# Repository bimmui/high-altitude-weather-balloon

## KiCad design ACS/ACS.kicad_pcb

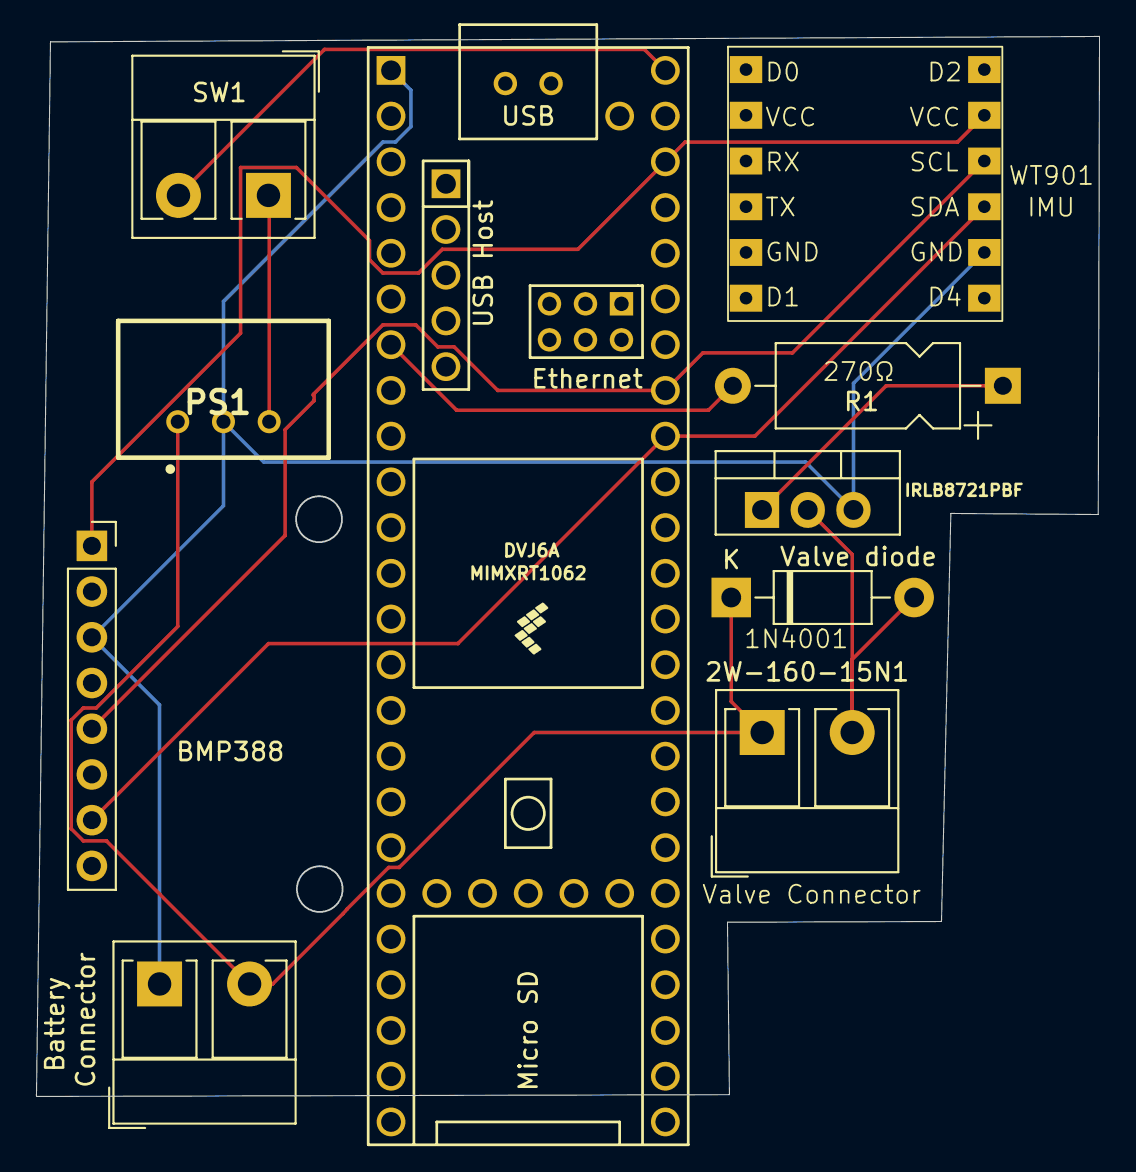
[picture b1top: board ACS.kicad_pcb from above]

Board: 2 copper layers, 59.0 x 58.8 mm, 10 parts (0 on the bottom side), 9 nets.

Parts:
2W-160-15N1: TerminalBlock_RND_205-00276_1x02_P5.00mm_Vertical
BMP388: PinSocket_1x08_P2.54mm_Vertical
Battery: Battery Screw_Terminal_01x02; TerminalBlock_RND_205-00276_1x02_P5.00mm_Vertical
IRLB8721PBF: IRLB8721PBF; TO-220-3_Vertical
PS1: TSR_1-2450; TSR-1-24120
R1: 270; CP_Axial_L10.0mm_D4.5mm_P15.00mm_Horizontal
SW1: SW_DPST_x2; TerminalBlock_RND_205-00276_1x02_P5.00mm_Vertical
U1: Teensy4.1; Teensy41
Valve diode: 1N4001; D_DO-41_SOD81_P10.16mm_Horizontal
WT901: WT901

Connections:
+3V3: BMP388.1 (VIN), U1.46 (3V3), WT901.8 (VCC)
+12V: 2W-160-15N1.1 (PWR), 2W-160-15N1.2 (GND), Battery.2, IRLB8721PBF.2 (D), PS1.1 (VIN+), Valve diode.1 (K), Valve diode.2 (A)
/5VIN: SW1.2 (B), U1.48 (VIN)
/SCL: BMP388.5 (SCK), U1.41 (19_A5_SCL), WT901.9 (SCL)
/SDA: BMP388.7 (SDA), U1.40 (18_A4_SDA), WT901.10 (SDA)
/Valve Signal: R1.2, U1.7 (5_IN2)
GND: BMP388.3 (GND), Battery.1, IRLB8721PBF.3 (S), PS1.2 (GND), U1.1 (GND), WT901.11 (GND)
unnamed: PS1.3 (VOUT+), SW1.1 (A)
unnamed: IRLB8721PBF.1 (G), R1.1

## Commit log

2024-07-20 added sensor and battery to schematic
2024-08-28 added valve symb and wires
2024-08-29 cleaned up valve symbol and partially completed wiring for valve control, teensy needs to be powered and connected to circuit
2024-09-26 added working valve control to schematic, named folders properly
2024-10-07 IMU Wiring
    Add wiring to WT901 IMU sensor
2024-10-09 fixed all the wiring, added footprints for some, and cleaned up the schematic
2024-10-10 added all components, just need to add footprints
2024-10-11 Oh wow, IMU working
    Add an example to run WT901 IMU, need to manually import library
2024-10-11 Moving files
    Sowwy, cleaning the repo
2024-10-13 Sunday Update
    integrated BMP388, WT901 and Solenoid. Update Schematic and add example code to test all component
2024-10-14 Add Switch and Heating Pad
    Added wiring for switch and heating pad for ACS. Fix wiring schematic IRLB8721 for solenoid control
2024-10-20 add cosmic watch stuff
2024-10-20 started the cosmic watch schematic, added some symbols and footprints relevant to it
2024-11-04 Add PCB
    Working on ACS PCB design...
2024-11-10 Making PCB rn
2024-11-10 Add footprint for WT901
2024-11-15 prototyped summing circuit and SiPM
2024-11-15 brought bill's changes
2024-11-17 added resistor footprints
2024-11-17 Assigned footprint to U2
2024-11-24 fixed error for U2
2024-11-24 Updated screw terminal and switch design
2024-12-02 made peak detector footprint
2024-12-03 finished traces for acs and generated gerber files
2024-12-27 grabbed c implementation of pid controller, rewrote it in python, trying to simulate controller with hab launch data
    TODO:
    - complete the dynamical model; need to figure out how to find the values to changing vars wrt to changing altitude
    - confirm that dvdt should have v^2 (looks weird)
    - runge katta velocity calculation
    - altitude estimation
    - everything else
2025-01-23 fuck
2025-02-19 Some pre changes tot he acs_sim, some ideas
2025-02-20 updated dynamical model of weather balloon
2025-02-20 forgot a few param definitions
2025-02-21 calculated rough initial pressure of the weather balloon
